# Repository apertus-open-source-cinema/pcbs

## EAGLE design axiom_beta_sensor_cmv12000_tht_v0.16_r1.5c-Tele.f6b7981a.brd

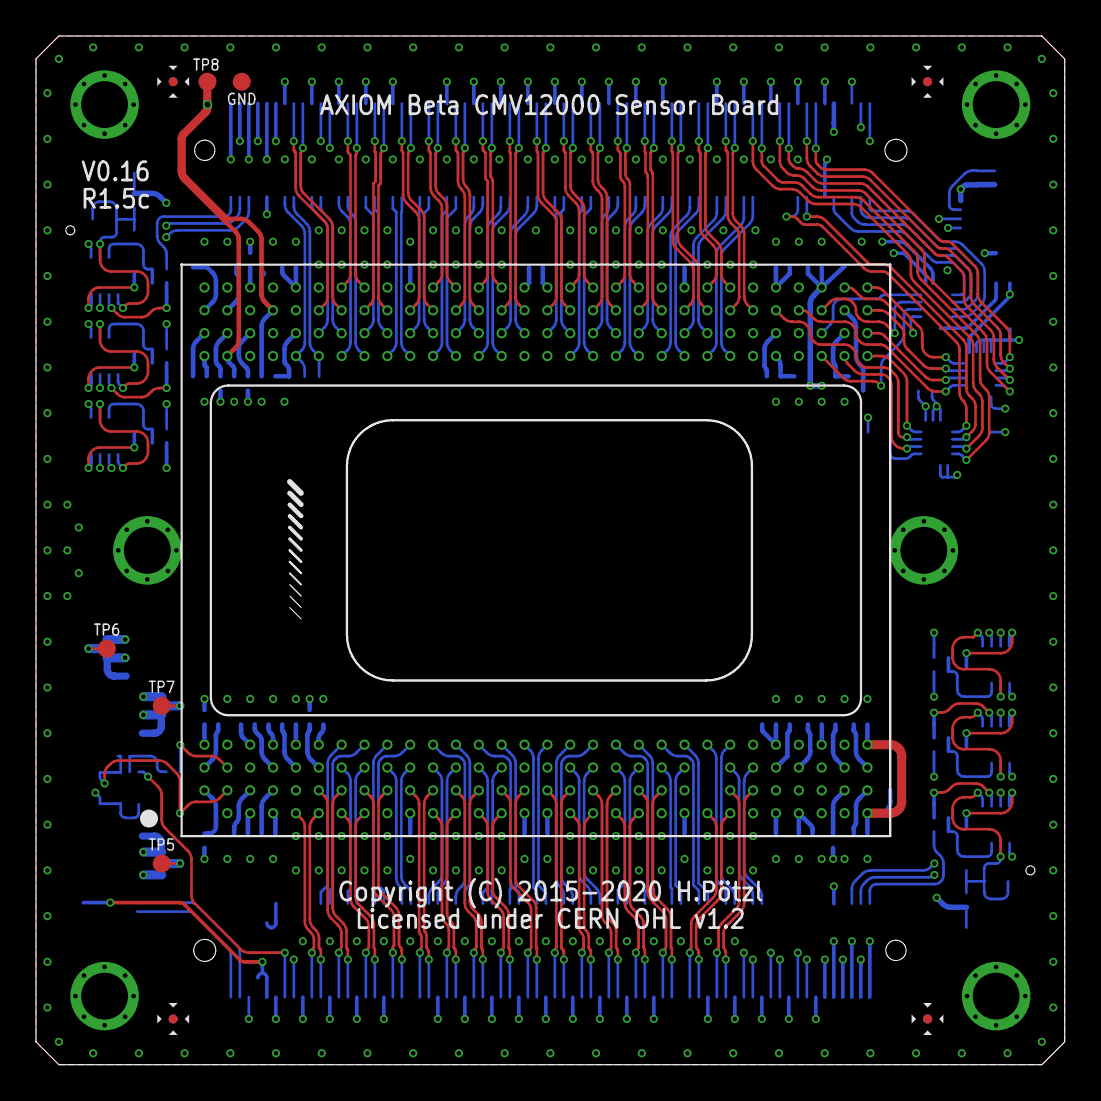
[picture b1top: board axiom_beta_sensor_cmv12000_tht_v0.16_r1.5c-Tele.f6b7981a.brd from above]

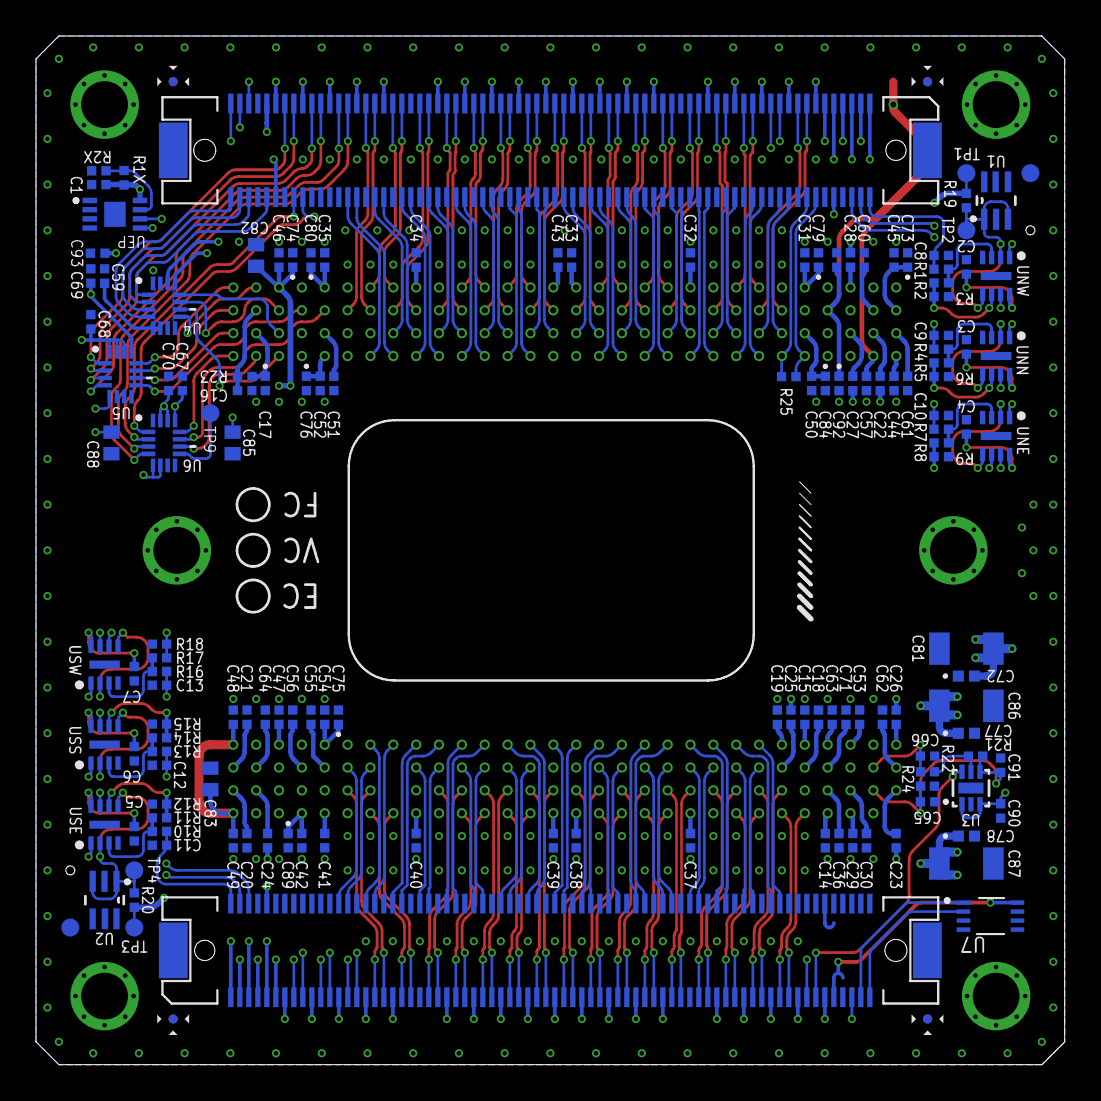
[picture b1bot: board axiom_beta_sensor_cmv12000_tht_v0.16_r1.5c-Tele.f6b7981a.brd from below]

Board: 4 copper layers, 57.1 x 57.1 mm, 159 parts (147 on the bottom side), 234 nets.

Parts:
C1, C2, C3, C4, C5, C6, C7, C14, C15, C16, C17, C18, C19, C20, C21, C22, C23, C24, C25, C26, C27, C28, C29, C30, C31, C32, C33, C34, C35, C36, C37, C38, C39, C40, C41, C42, C43, C44, C45, C46, C47, C48, C49, C50, C51, C52, C53, C54, C55, C56, C57, C58, C59, C60, C61, C62, C63, C64, C65, C66, C67, C68, C69, C70, C71, C93: 100n; 0402-C
C8, C9, C10, C11, C12, C13: 1µ; 0402-C
C72, C77, C78: 4µ7; 0402-B
C73, C74, C75, C76, C79, C80, C84, C89, C90, C91, C92: 4µ7; 0402-C
C81, C86, C87: 100µ; 1206-B
C82, C83, C85, C88: 10µ; 0603-C
FID1, FID2, FID3, FID4: FIDUCIAL; FID_ARROW
FID5, FID6, FID7, FID8: FIDUCIAL-3A; FID_3ARROW
GND, GND75, GND77: TPTP10R; TP10R
PARALLELLA: PARALLELLA-FRAME
R1, R7: 28k7; 0402-C
R1X: 10k; 0402-C
R2, R8: 3k32; 0402-C
R2X, R23, R24: 0R; 0402-C
R3, R9, R15, R18: 16k9; 0402-C
R4: 15k4; 0402-C
R5: 3k09; 0402-C
R6: 30k9; 0402-C
R10, R11, R12: 0402-C
R13: 22k6; 0402-C
R14: 9k53; 0402-C
R16: 18k7; 0402-C
R17: 13k3; 0402-C
R19, R20: 18k; 0402-C
R21: 5k9; 0402-C
R22: 14k3; 0402-C
R25: 100R; 0402-C
SENSOR: CMV12000ANDON; 10-30-07-237-400T4
TP1, TP2, TP3, TP4, TP5, TP6, TP7, TP8, TP9: TPTP10R; TP10R
U1, U2: TLV431DCK; SOT65P210X110-6N
U3: MIC47050; MLF-6
U4, U5, U6: SN74AVC4T774RSV; QFN40P185X265X55-16N
U7: LM75BGD; SOT996-2/3
U$1: µZ-FRAME
UEP: BR24G04NUX; DFN200X300X100-9N
UNE: TS332IQ2T; DFN200X200X100-9N
UNN: TS332IQ2T; DFN200X200X100-9N
UNW: TS332IQ2T; DFN200X200X100-9N
USE: TS332IQ2T; DFN200X200X100-9N
USS: TS332IQ2T; DFN200X200X100-9N
USW: TS332IQ2T; DFN200X200X100-9N
X-NORTH: FX10-144P; FX10A-144P
X-SOUTH: FX10-144P; FX10A-144P

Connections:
CLK_IN: SENSOR.E30, U6.12
FRAME_REQ: SENSOR.G30, U5.11
GND: C1.2, C2.2, C3.2, C4.2, C5.2, C6.2, C7.2, C8.2, C9.2, C10.2, C11.2, C12.2, C13.2, C14.2, C15.2, C16.2, C17.2, C18.2, C19.2, C20.2, C21.2, C29.2, C30.2, C31.2, C32.2, C33.2, C34.2, C35.2, C36.2, C37.2, C38.2, C39.2, C40.2, C41.2, C42.2, C43.2, C44.2, C45.2, C46.2, C47.2, C48.2, C49.2, C50.2, C51.2, C52.2, C53.2, C54.2, C55.2, C56.2, C57.2, C58.2, C59.2, C60.2, C61.2, C62.2, C63.2, C64.2, C65.2, C66.2, C67.2, C68.2, C69.2, C70.2, C71.2, C72.2, C73.2, C74.2, C75.2, C76.2, C77.2, C78.2, C79.2, C80.2, C81.2, C82.2, C83.2, C84.2, C85.2, C86.2, C87.2, C88.2, C89.2, C90.2, C91.1, C92.2, C93.2, GND.TP, GND75.TP, GND77.TP, R2X.2, R3.2, R6.2, R9.2, R12.2, R15.2, R18.2, R22.1, SENSOR.A9, SENSOR.A21, SENSOR.A25, SENSOR.A28, SENSOR.A29, SENSOR.B5, SENSOR.B22, SENSOR.B26, SENSOR.B27, SENSOR.B28, SENSOR.C15, SENSOR.C16, SENSOR.C28, SENSOR.D2, SENSOR.D25, SENSOR.D27, SENSOR.D29, SENSOR.E3, SENSOR.E4, SENSOR.E15, SENSOR.E16, SENSOR.E25, SENSOR.E27, SENSOR.F4, SENSOR.F27, SENSOR.G3, SENSOR.G5, SENSOR.H1, SENSOR.H4, SENSOR.H6, SENSOR.H9, SENSOR.H21, SENSOR.H25, SENSOR.H27, U1.6, U2.6, U3.2, U3.EP, U4.7, U4.8, U4.16, U5.6, U5.7, U5.8, U6.7, U6.8, U6.16, U7.4, U7.5, U7.6, U7.7, UEP.1, UEP.2, UEP.3, UEP.4, UEP.EP, UNE.4, UNE.EP, UNN.4, UNN.EP, UNW.4, UNW.EP, USE.4, USE.EP, USS.4, USS.EP, USW.4, USW.EP, X-NORTH.12, X-NORTH.18, X-NORTH.24, X-NORTH.30, X-NORTH.36, X-NORTH.42, X-NORTH.43, X-NORTH.48, X-NORTH.54, X-NORTH.60, X-NORTH.66, X-NORTH.72, X-NORTH.78, X-NORTH.84, X-NORTH.90, X-NORTH.96, X-NORTH.102, X-NORTH.103, X-NORTH.108, X-NORTH.114, X-NORTH.120, X-NORTH.126, X-NORTH.132, X-NORTH.138, X-NORTH.139, X-SOUTH.12, X-SOUTH.18, X-SOUTH.24, X-SOUTH.30, X-SOUTH.36, X-SOUTH.42, X-SOUTH.43, X-SOUTH.48, X-SOUTH.54, X-SOUTH.60, X-SOUTH.66, X-SOUTH.72, X-SOUTH.78, X-SOUTH.84, X-SOUTH.90, X-SOUTH.96, X-SOUTH.102, X-SOUTH.103, X-SOUTH.108, X-SOUTH.114, X-SOUTH.120, X-SOUTH.126, X-SOUTH.132, X-SOUTH.138, X-SOUTH.139
N00_N: R25.2, SENSOR.E6, X-NORTH.16
N00_P: R25.1, SENSOR.E5, X-NORTH.14
N01_N: SENSOR.G7, X-NORTH.17
N01_P: SENSOR.G6, X-NORTH.15
N02_N: SENSOR.F7, X-NORTH.22
N02_P: SENSOR.F6, X-NORTH.20
N04_N: SENSOR.E8, X-NORTH.28
N04_P: SENSOR.E7, X-NORTH.26
N05_N: SENSOR.H8, X-NORTH.29
N05_P: SENSOR.H7, X-NORTH.27
N06_N: SENSOR.F9, X-NORTH.34
N06_P: SENSOR.F8, X-NORTH.32
N07_N: SENSOR.G9, X-NORTH.35
N07_P: SENSOR.G8, X-NORTH.33
N08_N: SENSOR.E10, X-NORTH.40
N08_P: SENSOR.E9, X-NORTH.38
N09_N: SENSOR.G11, X-NORTH.41
N09_P: SENSOR.G10, X-NORTH.39
N10_N: SENSOR.F11, X-NORTH.46
N10_P: SENSOR.F10, X-NORTH.44
N11_N: SENSOR.H12, X-NORTH.47
N11_P: SENSOR.H11, X-NORTH.45
N12_N: SENSOR.E12, X-NORTH.52
N12_P: SENSOR.E11, X-NORTH.50
N13_N: SENSOR.G13, X-NORTH.53
N13_P: SENSOR.G12, X-NORTH.51
N14_N: SENSOR.F13, X-NORTH.58
N14_P: SENSOR.F12, X-NORTH.56
N15_N: SENSOR.H14, X-NORTH.59
N15_P: SENSOR.H13, X-NORTH.57
N16_N: SENSOR.E14, X-NORTH.64
N16_P: SENSOR.E13, X-NORTH.62
N17_N: SENSOR.G15, X-NORTH.65
N17_P: SENSOR.G14, X-NORTH.63
N18_N: SENSOR.F15, X-NORTH.70
N18_P: SENSOR.F14, X-NORTH.68
N19_N: SENSOR.G17, X-NORTH.71
N19_P: SENSOR.G16, X-NORTH.69
N20_N: SENSOR.F17, X-NORTH.76
N20_P: SENSOR.F16, X-NORTH.74
N21_N: SENSOR.H18, X-NORTH.77
N21_P: SENSOR.H17, X-NORTH.75
N22_N: SENSOR.E18, X-NORTH.82
N22_P: SENSOR.E17, X-NORTH.80
N23_N: SENSOR.G19, X-NORTH.83
N23_P: SENSOR.G18, X-NORTH.81
N24_N: SENSOR.F19, X-NORTH.88
N24_P: SENSOR.F18, X-NORTH.86
N25_N: SENSOR.H20, X-NORTH.89
N25_P: SENSOR.H19, X-NORTH.87
N26_N: SENSOR.E20, X-NORTH.94
N26_P: SENSOR.E19, X-NORTH.92
N27_N: SENSOR.G21, X-NORTH.95
N27_P: SENSOR.G20, X-NORTH.93
N28_N: SENSOR.F21, X-NORTH.100
N28_P: SENSOR.F20, X-NORTH.98
N29_N: SENSOR.G23, X-NORTH.101
N29_P: SENSOR.G22, X-NORTH.99
N30_N: SENSOR.E22, X-NORTH.106
N30_P: SENSOR.E21, X-NORTH.104
N31_N: SENSOR.H24, X-NORTH.107
N31_P: SENSOR.H23, X-NORTH.105
N32_N: SENSOR.F23, X-NORTH.112
N32_P: SENSOR.F22, X-NORTH.110
N33_N: SENSOR.G25, X-NORTH.113
N33_P: SENSOR.G24, X-NORTH.111
N34_N: SENSOR.E24, X-NORTH.118
N34_P: SENSOR.E23, X-NORTH.116
N35_N: U6.4, X-NORTH.119
N35_P: U6.3, X-NORTH.117
N37_N: U5.3, X-NORTH.125
N37_P: U5.4, X-NORTH.123
N38_N: U6.2, X-NORTH.130
N38_P: U6.1, X-NORTH.128
N39_N: U5.1, X-NORTH.131
N39_P: U5.2, X-NORTH.129
unnamed: R1X.2, R2X.1, UEP.7
unnamed: C60.1, SENSOR.G2
unnamed: C61.1, SENSOR.F1
unnamed: TP9.TP, U6.9
unnamed: C62.1, SENSOR.C1
unnamed: C63.1, SENSOR.D4
unnamed: C64.1, SENSOR.C29
unnamed: C71.1, SENSOR.C4
unnamed: C14.1, SENSOR.A4
unnamed: C15.1, SENSOR.D5
unnamed: R21.1, R22.2, U3.5
unnamed: C18.1, SENSOR.C5
unnamed: C19.1, SENSOR.D6
unnamed: C20.1, SENSOR.B30
unnamed: C21.1, SENSOR.C30
unnamed: C22.2, SENSOR.F2
unnamed: C23.2, SENSOR.B1
unnamed: C24.2, SENSOR.B29
unnamed: C25.2, SENSOR.C6
unnamed: C26.2, SENSOR.D1
unnamed: C27.2, SENSOR.F3
unnamed: C28.2, SENSOR.H3
unnamed: C29.1, SENSOR.A3
unnamed: C30.1, SENSOR.B3
unnamed: R11.2, R12.1, USE.6
unnamed: R5.2, R6.1, UNN.6
unnamed: R8.2, R9.1, UNE.6
unnamed: R10.2, R11.1, USE.3
unnamed: R7.2, R8.1, UNE.3
unnamed: R1.2, R2.1, UNW.3
unnamed: R2.2, R3.1, UNW.6
unnamed: R14.2, R15.1, USS.6
unnamed: R13.2, R14.1, USS.3
unnamed: R16.2, R17.1, USW.3
unnamed: R17.2, R18.1, USW.6
N_CHK_V: C2.1, C3.1, C4.1, R19.1, TP1.TP, UNE.8, UNN.8, UNW.8, X-NORTH.10
N_I2C_V: C1.1, R1X.1, UEP.8, X-NORTH.135
N_REF: R19.2, TP2.TP, U1.1, U1.3, UNE.2, UNE.5, UNN.2, UNN.5, UNW.2, UNW.5
N_SCK: U4.4, X-NORTH.144
N_SCL: UEP.6, X-NORTH.143
N_SDA: UEP.5, X-NORTH.141
N_SDI: U4.2, X-NORTH.140
N_SDO: U4.3, X-NORTH.142
N_SPI_EN: U4.1, X-NORTH.136
N_SPI_V: C59.1, U4.5, U4.6, U4.14, U4.15, X-NORTH.134
N_VE: C22.1, C23.1, C24.1, C25.1, C26.1, C27.1, C28.1, C50.1, C51.1, C52.1, C53.1, C54.1, C55.1, C56.1, C67.1, C69.1, C75.1, C76.1, C77.1, C84.1, C85.1, C86.1, C93.1, SENSOR.C26, SENSOR.C27, SENSOR.D3, SENSOR.D26, SENSOR.E26, SENSOR.F5, SENSOR.F26, TP7.TP, U4.13, U5.13, U6.13, X-NORTH.109, X-NORTH.115, X-NORTH.121, X-NORTH.127, X-NORTH.133
N_VE_CV: C10.1, R7.1, X-NORTH.6
N_VE_OV: UNE.7, X-NORTH.5
N_VE_UV: UNE.1, X-NORTH.11
N_VN: C31.1, C32.1, C33.1, C34.1, C35.1, C36.1, C37.1, C38.1, C39.1, C40.1, C41.1, C42.1, C43.1, C44.1, C68.1, C70.1, C78.1, C79.1, C80.1, C87.1, C88.1, C89.1, SENSOR.A10, SENSOR.A15, SENSOR.A16, SENSOR.A22, SENSOR.A26, SENSOR.A27, SENSOR.B4, SENSOR.E1, SENSOR.H5, SENSOR.H10, SENSOR.H15, SENSOR.H16, SENSOR.H22, SENSOR.H26, TP5.TP, U5.5, U5.14, U5.15, U5.16, U6.5, U6.6, U6.14, U6.15, X-NORTH.49, X-NORTH.55, X-NORTH.61, X-NORTH.67, X-NORTH.73, X-NORTH.79, X-NORTH.85, X-NORTH.91, X-NORTH.97
N_VN_CV: C9.1, R4.1, X-NORTH.4
N_VN_OV: UNN.7, X-NORTH.3
N_VN_UV: UNN.1, X-NORTH.9
N_VW: C57.1, C58.1, C92.1, SENSOR.E2, SENSOR.G4, TP8.TP, X-NORTH.13, X-NORTH.19, X-NORTH.25, X-NORTH.31, X-NORTH.37
N_VW_CV: C8.1, R1.1, X-NORTH.2
N_VW_OV: UNW.7, X-NORTH.1
N_VW_UV: UNW.1, X-NORTH.7
R5: R4.2, R5.1, UNN.3
S04_N: SENSOR.C24, X-SOUTH.28
S04_P: SENSOR.C25, X-SOUTH.26
S06_N: SENSOR.D23, X-SOUTH.34
S06_P: SENSOR.D24, X-SOUTH.32
S07_N: SENSOR.B24, X-SOUTH.35
S07_P: SENSOR.B25, X-SOUTH.33
S08_N: SENSOR.D21, X-SOUTH.40
S08_P: SENSOR.D22, X-SOUTH.38
S09_N: SENSOR.A23, X-SOUTH.41
S09_P: SENSOR.A24, X-SOUTH.39
S10_N: SENSOR.C21, X-SOUTH.46
S10_P: SENSOR.C22, X-SOUTH.44
S11_N: SENSOR.B20, X-SOUTH.47
S11_P: SENSOR.B21, X-SOUTH.45
S12_N: SENSOR.D19, X-SOUTH.52
S12_P: SENSOR.D20, X-SOUTH.50
S13_N: SENSOR.A19, X-SOUTH.53
S13_P: SENSOR.A20, X-SOUTH.51
S14_N: SENSOR.C19, X-SOUTH.58
S14_P: SENSOR.C20, X-SOUTH.56
S15_N: SENSOR.B18, X-SOUTH.59
S15_P: SENSOR.B19, X-SOUTH.57
S16_N: SENSOR.C17, X-SOUTH.64
S16_P: SENSOR.C18, X-SOUTH.62
S17_N: SENSOR.A17, X-SOUTH.65
S17_P: SENSOR.A18, X-SOUTH.63
S18_N: SENSOR.D17, X-SOUTH.70
S18_P: SENSOR.D18, X-SOUTH.68
S19_N: SENSOR.B16, X-SOUTH.71
S19_P: SENSOR.B17, X-SOUTH.69
S20_N: SENSOR.D15, X-SOUTH.76
S20_P: SENSOR.D16, X-SOUTH.74
S21_N: SENSOR.B14, X-SOUTH.77
S21_P: SENSOR.B15, X-SOUTH.75
S22_N: SENSOR.D13, X-SOUTH.82
S22_P: SENSOR.D14, X-SOUTH.80
S23_N: SENSOR.A13, X-SOUTH.83
S23_P: SENSOR.A14, X-SOUTH.81
S24_N: SENSOR.C13, X-SOUTH.88
S24_P: SENSOR.C14, X-SOUTH.86
S25_N: SENSOR.B12, X-SOUTH.89
S25_P: SENSOR.B13, X-SOUTH.87
S26_N: SENSOR.D11, X-SOUTH.94
S26_P: SENSOR.D12, X-SOUTH.92
S27_N: SENSOR.A11, X-SOUTH.95
S27_P: SENSOR.A12, X-SOUTH.93
S28_N: SENSOR.C11, X-SOUTH.100
S28_P: SENSOR.C12, X-SOUTH.98
S29_N: SENSOR.B10, X-SOUTH.101
S29_P: SENSOR.B11, X-SOUTH.99
S30_N: SENSOR.C9, X-SOUTH.106
S30_P: SENSOR.C10, X-SOUTH.104
S31_N: SENSOR.B8, X-SOUTH.107
S31_P: SENSOR.B9, X-SOUTH.105
S32_N: SENSOR.D9, X-SOUTH.112
S32_P: SENSOR.D10, X-SOUTH.110
S33_N: SENSOR.A7, X-SOUTH.113
S33_P: SENSOR.A8, X-SOUTH.111
S34_N: SENSOR.C7, X-SOUTH.118
S34_P: SENSOR.C8, X-SOUTH.116
S35_N: SENSOR.B6, X-SOUTH.119
S35_P: SENSOR.B7, X-SOUTH.117
S36_N: SENSOR.D7, X-SOUTH.124
S36_P: SENSOR.D8, X-SOUTH.122
S37_N: SENSOR.A5, X-SOUTH.125
S37_P: SENSOR.A6, X-SOUTH.123
S39_N: U3.6, X-SOUTH.131
SPI_CLK: SENSOR.H29, U4.9
SPI_EN: SENSOR.F28, U4.12
SPI_IN: SENSOR.E28, U4.10
SPI_OUT: SENSOR.G28, U4.11
SYS_RES_N: SENSOR.F30, U5.10
S_CHK_V: C5.1, C6.1, C7.1, R20.1, TP3.TP, USE.8, USS.8, USW.8, X-SOUTH.10
S_I2C_V: U7.8, X-SOUTH.135
S_REF: R20.2, TP4.TP, U2.1, U2.3, USE.2, USE.5, USS.2, USS.5, USW.2, USW.5
S_SCL: U7.2, X-SOUTH.143
S_SDA: U7.1, X-SOUTH.141
S_VE: X-SOUTH.13, X-SOUTH.19, X-SOUTH.25, X-SOUTH.31, X-SOUTH.37
S_VE_CV: C11.1, R10.1, X-SOUTH.2
S_VE_OV: USE.7, X-SOUTH.1
S_VE_UV: USE.1, X-SOUTH.7
S_VS: C45.1, C46.1, C47.1, C48.1, C49.1, C72.1, C73.1, C74.1, C81.1, C82.1, C83.1, SENSOR.A30, SENSOR.D28, SENSOR.D30, SENSOR.G1, SENSOR.H28, TP6.TP, X-SOUTH.49, X-SOUTH.55, X-SOUTH.61, X-SOUTH.67, X-SOUTH.73, X-SOUTH.79, X-SOUTH.85, X-SOUTH.91, X-SOUTH.97
S_VS_CV: C12.1, R13.1, X-SOUTH.4
S_VS_OV: USS.7, X-SOUTH.3
S_VS_UV: USS.1, X-SOUTH.9
S_VW: C90.1, U3.1, U3.3, X-SOUTH.109, X-SOUTH.115, X-SOUTH.121, X-SOUTH.127, X-SOUTH.133
S_VW_CV: C13.1, R16.1, X-SOUTH.6
S_VW_OV: USW.7, X-SOUTH.5
S_VW_UV: USW.1, X-SOUTH.11
TDIG1: SENSOR.G27, U5.9
TDIG2: SENSOR.G26, U6.11
T_EXP1: SENSOR.H30, U5.12
T_EXP2: SENSOR.E29, U6.10
VRAMP1: C16.1, R23.1, SENSOR.G29
VRAMP2: C17.1, R23.2, SENSOR.F29
VTREF: C65.1, C91.2, R21.2, R24.1, SENSOR.B2, U3.4
VTSIG: C66.1, R24.2, SENSOR.C2

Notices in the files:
axiom_beta_sensor_cmv12000_tht_v0.16_r1.5c-Tele.f6b7981a.brd:
Copyright (C) 2015-2020 H.Pötzl
Licensed under CERN OHL v1.2
